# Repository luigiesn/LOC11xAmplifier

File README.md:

# LOC11xAmplifier
An optically insulated amplifier with 4x gain / Um amplificador isolado opticamente com ganho de 4x

O amplificador é baseado no optoacoplador linear [LOC110S/P](circuit/kicadlib/datasheet/LOC110.pdf) e foi projetado a fim de testar a técnica de se utilizar um par óptico casado de fotodiodos para fazer um circuito isolado e realimentado simultâneamente.

O projeto foi feito agora precisa ser testado :)

## Especificações

### Condições de Operação Recomendadas¹

| Parâmetro | Condições | Símbolo | Mín. |Típico | Máx. | Unidade |
| :------- | :-------: | :-------: | :-------: | :-------: | :-------: | :-------: |
| **Alimentação** |
| Tensão de Alimentação do Estágio de Entrada | - | Vs_1 | 3.15 | - | 3.75 | V |
| Tensão de Alimentação do Estágio de Saída | - | Vs_2 | 3.02 | - | 4.36 | V |
| Corrente Quiescente do Estágio de Entrada | Vs_1 = 3.3 V, V_in = 0 | I_q1 | - | 6.98 | - | mA |
| Corrente Quiescente do Estágio de Saída | Vs_2 = 3.3 V, V_in = 0 | I_q2 | - | 3.3 | - | mA |
| **Amplificador** |
| Tensão de Entrada | - | V_in | -250 | - | 250 | mV |
| Impedância de Entrada |  - | Z_in | - | 60.44 | - | kΩ |
| Tensão de _Offset_ de Saída | - | V_off | - | 1.535 | - | V |
| Corrente Máxima de Saída | Vs_2 = 3.15 V |  | - | - | 1.5 |  |
|                          | Vs_2 = 3.3 V | I_o | - | - | 3.1 | mA |
|                          | Vs_2 = 3.5 V | | - | - | 5.3 |  |
| Ganho de Tensão |  - | A_v | - | 3.98 | - |  |
| Resposta de frequência² | - | f_-3db | - | 200 | - | kHz
###### ¹ valores calculados para 25°C
###### ² valor com referência no modo de operação fotocondutiva dos fotodiodos

## O circuito

Os componentes e topologias do circuito foram escolhidos a fim de obter baixo custo, mas com especificações razoáveis. Suas conexões estão disponíveis para barras de pinos de 2.54 mm de espaçamento e pads nas bordas para uma soldagem SMT

O circuito opera nominalmente com tensões de alimentação de 3.3 V, faixas de entrada de ±250 mV e tensão de saída centralizada em 1.535 V e ganho de 3.98 do sinal de entrada.

Em função da configuração fotocondutiva dos [pares ópticos](circuit/kicadlib/datasheet/LOC110.pdf), o circuito opera até 200 kHz. 

#### Operação

O estágio de entrada foi projetado para operar na faixa de 2.5 até 3.5 mA do diodo emissor. Essa região foi escolhida por resultar em uma baixa variação de ganho do sinal em 25 °C. 

Seus [amplificadores](circuit/kicadlib/datasheet/tlv9001.pdf) são _rail-to-rail_ para entradas e saída com baixo _offset_ de entrada e baixo consumo (1 μA)

As [referências de tensão](circuit/kicadlib/datasheet/lm4040-n.pdf) são de 2 % do tipo _shunt_

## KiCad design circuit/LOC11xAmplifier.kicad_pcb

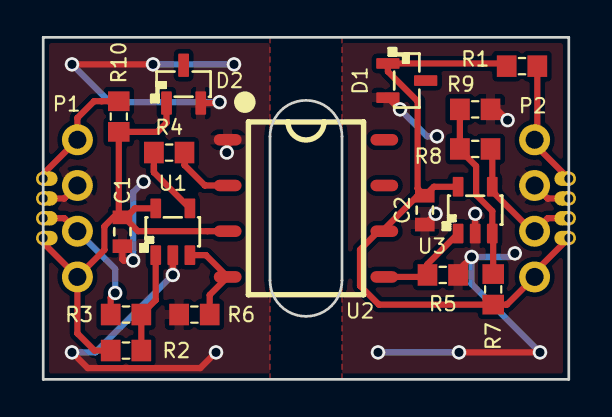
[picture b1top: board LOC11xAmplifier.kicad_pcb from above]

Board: 2 copper layers, 29.2 x 19.0 mm, 19 parts (0 on the bottom side), 14 nets.

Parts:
C1, C2: CC0603MRY5V6BB105; CAP_0603
D1, D2: LM4040EIM3X-3.0_NOPB; SOT23-3_LM4040N
P1, P2: 4P_PLATING1.1MM_HOLE2.54MM
R1: RC0603FR-0791RL; RES_0603
R2: RC0603FR-07180KL; RES_0603
R3: RC0603FR-0791KL; RES_0603
R4: RC0603FR-07430RL; RES_0603
R5, R9: RC0603FR-0775KL; RES_0603
R6: RC0603FR-0734K8L; RES_0603
R7: RC0603FR-0714KL; RES_0603
R8: RC0603FR-0721KL; RES_0603
R10: RC0603FR-0743RL; RES_0603
U1, U3: TLV9001UIDBVR; SOT23-5_TLV9001
U2: LOC110PTR; SO8_LOC110P

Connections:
/IN_3VREF: C1.2, D2.1, P1.4, R2.1, R10.1, U1.5, U2.3
/IN_GND: C1.1, D2.2, P1.2, R6.1, U1.2, U2.1
/IN_SUP: P1.1, R10.2
/OUT_3VREF: C2.2, D1.1, P2.1, R1.1, R7.2, U2.6, U3.5
/OUT_GND: C2.1, D1.2, P2.3, R5.2, R9.2, U3.2
/OUT_SUP: P2.4, R1.2
/VIN: P1.3, R3.2
/VOUT: P2.2, R8.1, U3.4
unnamed: R2.2, R3.1, U1.1
unnamed: R4.1, U2.2
unnamed: R4.2, U1.4
unnamed: R5.1, U2.5, U3.1
unnamed: R6.2, U1.3, U2.4
unnamed: R7.1, R8.2, R9.1, U3.3

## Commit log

2019-05-03 Primeiro commit
    Primeira versão do amplificador. Inclusão de:
    - datasheets
    - bibliotecas
    - esquemático e layout
2019-05-03 Inclusão de arquivos de pré-visualização
    Disponibilização de imagens em perpectiva da placa e esquemático em .pdf
2019-05-03 Inclusão de resistor
    RC0603FR-0743RL incluído na biblioteca
2019-05-03 Adicionada descrição do circuito
    Adicionada especificações e detalhes de operação do circuito
2019-05-04 Atualizando o esquemático em pdf
    Alterado resistor R10 de 91ohms para 43ohms
2019-05-04 Criado template próprio
2019-05-04 Alterado o esquemático
    - Atualizada versão do esquemático para v1.1
    - Incluido endereço do repositório
    - Alterado layout da worksheet
2019-05-04 Atualizado o esquemático .pdf
    - Atualizado para a v1.1
2019-05-04 Alterado rodapé
    - aplicado novo worksheet
    - adicionada descrição no rodopé
2019-05-04 Corrigida unidade na tabela
2019-05-04 Incluídos 3D na biblioteca
    Incluídos? SSO8, SOT23-3 e SOT23-5
2019-05-04 Incluídos 3Ds nos footprints
    SO8_LOC110P, SOT23-3_LM4040N e SOT23-5_TLV9001
2019-05-04 Atualizado layout
    Atualizados footprints com 3D
2019-05-04 Nova renderização
    Atualização dos footprints e aplicado raytracing
2019-05-04 Adicionados prints dos gerbers
